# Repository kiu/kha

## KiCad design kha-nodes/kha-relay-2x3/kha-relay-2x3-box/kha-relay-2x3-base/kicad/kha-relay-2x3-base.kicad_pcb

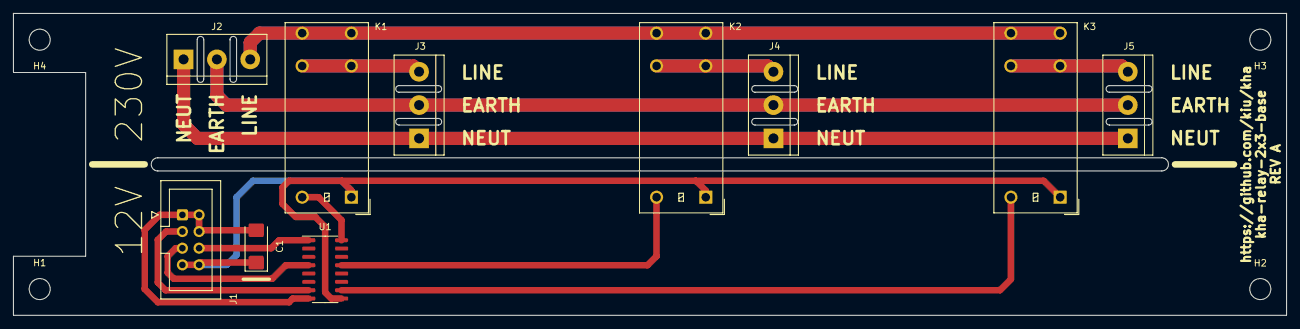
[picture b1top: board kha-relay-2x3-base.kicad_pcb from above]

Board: 2 copper layers, 194.0 x 46.0 mm, 14 parts (0 on the bottom side), 14 nets.

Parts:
C1: 220uF; CP_EIA-6032-28_Kemet-C
H1, H2, H3, H4: MountingHole; MountingHole_3.2mm_M3_DIN965
J1: Conn_02x04_Odd_Even; IDC-Header_2x04_P2.54mm_Vertical
J2, J3, J4, J5: Conn_01x03; TerminalBlock_bornier-3_P5.08mm
K1, K2, K3: G2RL-1A-E; Relay_SPST_Omron_G2RL-1A-E
U1: ULN2003; SOP-16_3.9x9.9mm_P1.27mm

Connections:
+12V: C1.1, J1.7, J1.8, K1.A1, K2.A1, K3.A1, U1.9 (COM)
Earth: J2.2, J3.2, J4.2, J5.2
GND: C1.2, J1.1, J1.2, J1.4, U1.8 (GND)
LINE: J2.3, K1.14, K2.14, K3.14
NEUT: J2.1, J3.1, J4.1, J5.1
unnamed: J1.3, U1.7 (I7)
unnamed: J1.5, U1.4 (I4)
unnamed: J1.6, U1.1 (I1)
unnamed: J3.3, K1.13
unnamed: J4.3, K2.13
unnamed: J5.3, K3.13
R01: K1.A2, U1.16 (O1)
R02: K2.A2, U1.13 (O4)
R03: K3.A2, U1.10 (O7)

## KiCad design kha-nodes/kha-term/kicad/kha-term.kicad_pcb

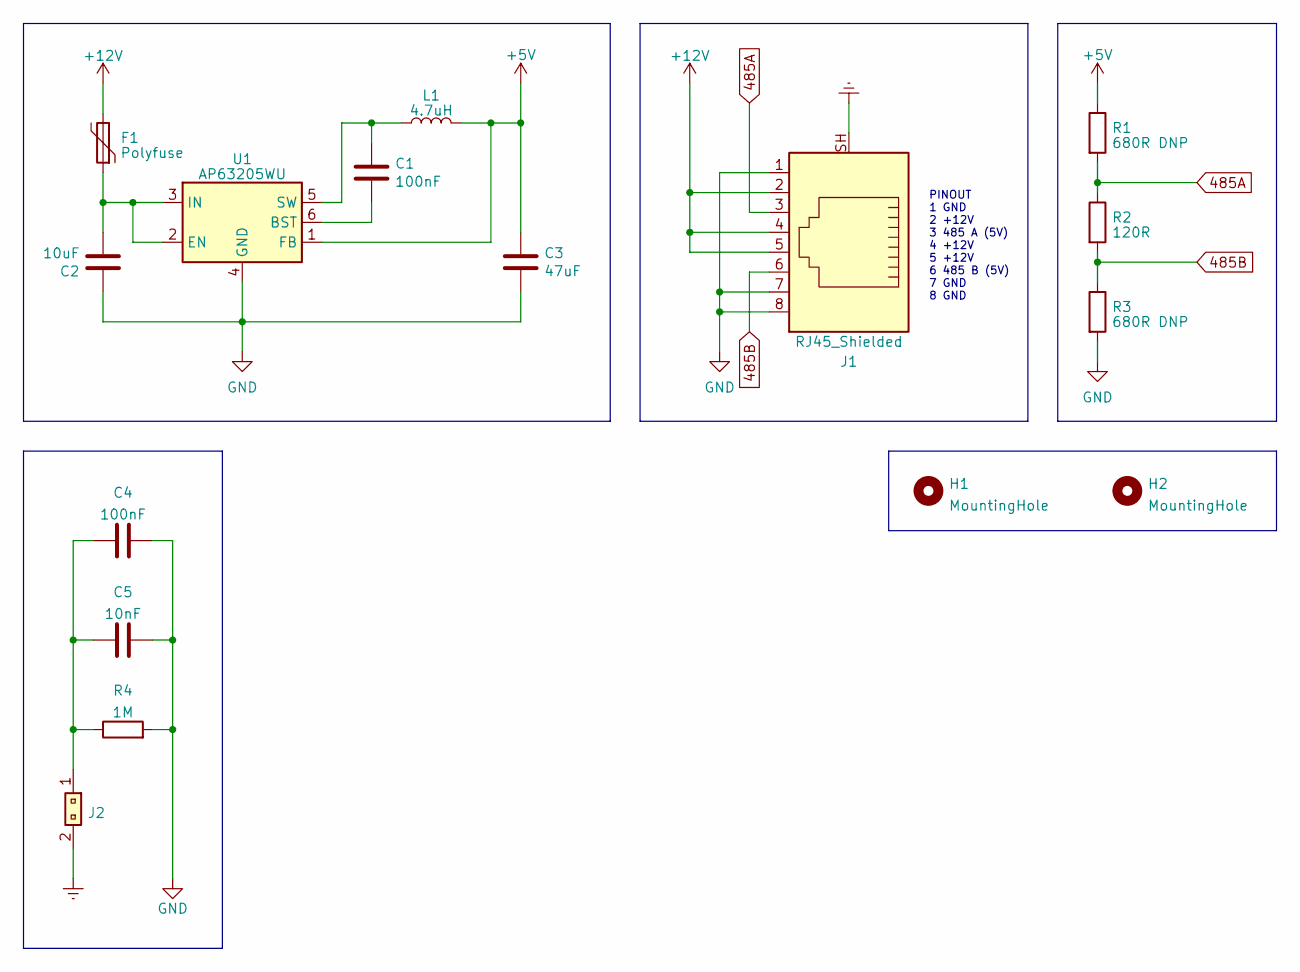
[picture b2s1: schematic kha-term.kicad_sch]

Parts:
C1, C4: 100nF; C_0805_2012Metric
C2: 10uF; C_0805_2012Metric
C3: 47uF; C_1210_3225Metric
C5: 10nF; C_0805_2012Metric
F1: Polyfuse; Fuse_0805_2012Metric
H1, H2: MountingHole; MountingHole_3.7mm
J1: RJ45_Shielded; GDLX-S-88K
J2: 1x02_Jumper; PinHeader_1x02_P2.54mm_Vertical
L1: 4.7uH; L_1210_3225Metric
R1, R3: 680R DNP; R_0805_2012Metric
R2: 120R; R_0805_2012Metric
R4: 1M; R_0805_2012Metric
U1: AP63205WU; TSOT-23-6

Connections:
485A: J1.3, R1.2, R2.1
485B: J1.6, R2.2, R3.1
+5V: C3.1, L1.2, R1.1, U1.1 (FB)
+12V: F1.2, J1.2, J1.4, J1.5
Earth: J1.SH, J2.2
GND: C2.1, C3.2, C4.2, C5.2, J1.1, J1.7, J1.8, R3.2, R4.2, U1.4 (GND)
unnamed: C4.1, C5.1, J2.1, R4.1
unnamed: C1.2, U1.6 (BST)
unnamed: C2.2, F1.1, U1.2 (EN), U1.3 (IN)
unnamed: C1.1, L1.1, U1.5 (SW)

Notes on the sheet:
PINOUT 1 GND 2 +12V 3 485 A (5V) 4 +12V 5 +12V 6 485 B (5V) 7 GND 8 GND

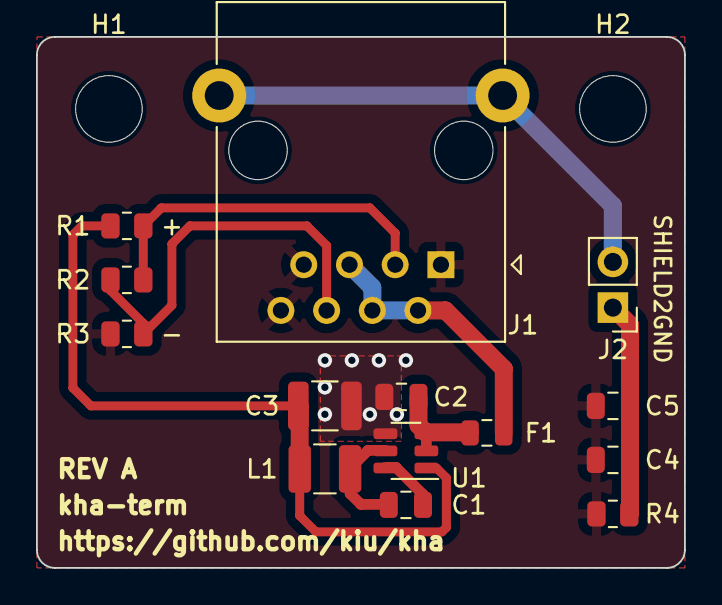
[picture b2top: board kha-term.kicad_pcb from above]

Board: 2 copper layers, 36.0 x 29.5 mm, 16 parts (0 on the bottom side), 10 nets.

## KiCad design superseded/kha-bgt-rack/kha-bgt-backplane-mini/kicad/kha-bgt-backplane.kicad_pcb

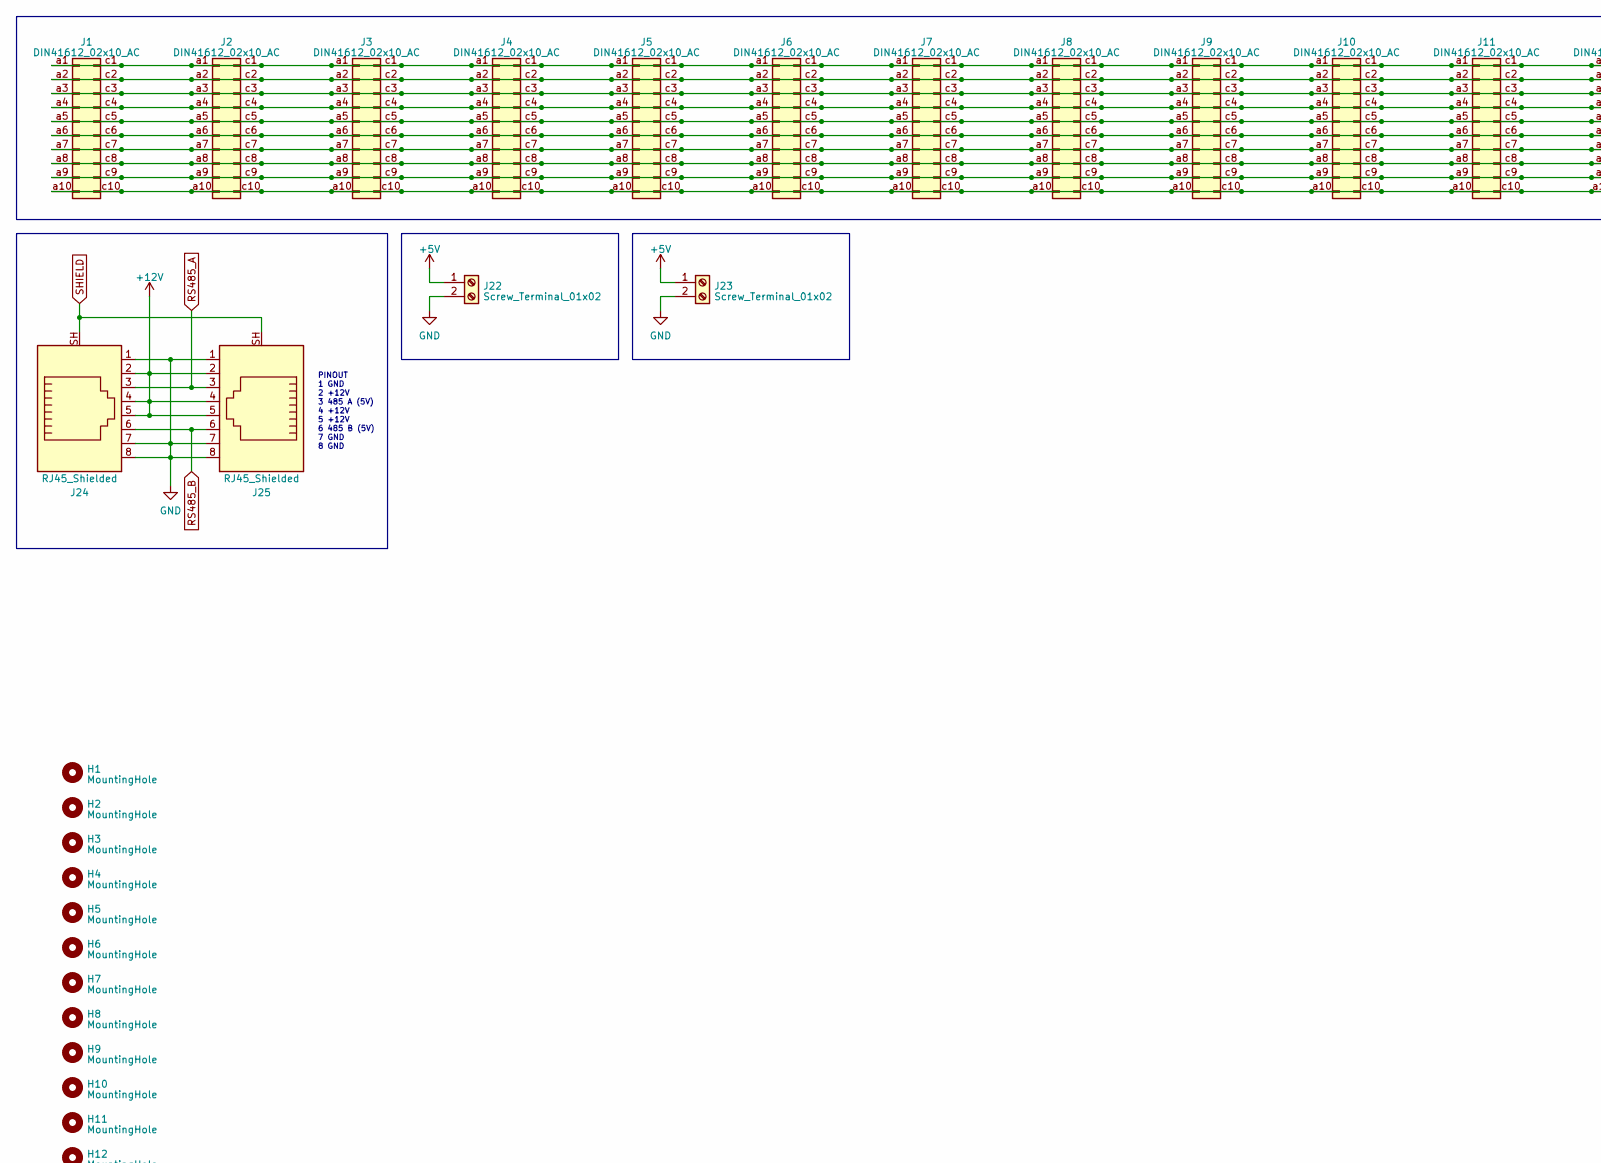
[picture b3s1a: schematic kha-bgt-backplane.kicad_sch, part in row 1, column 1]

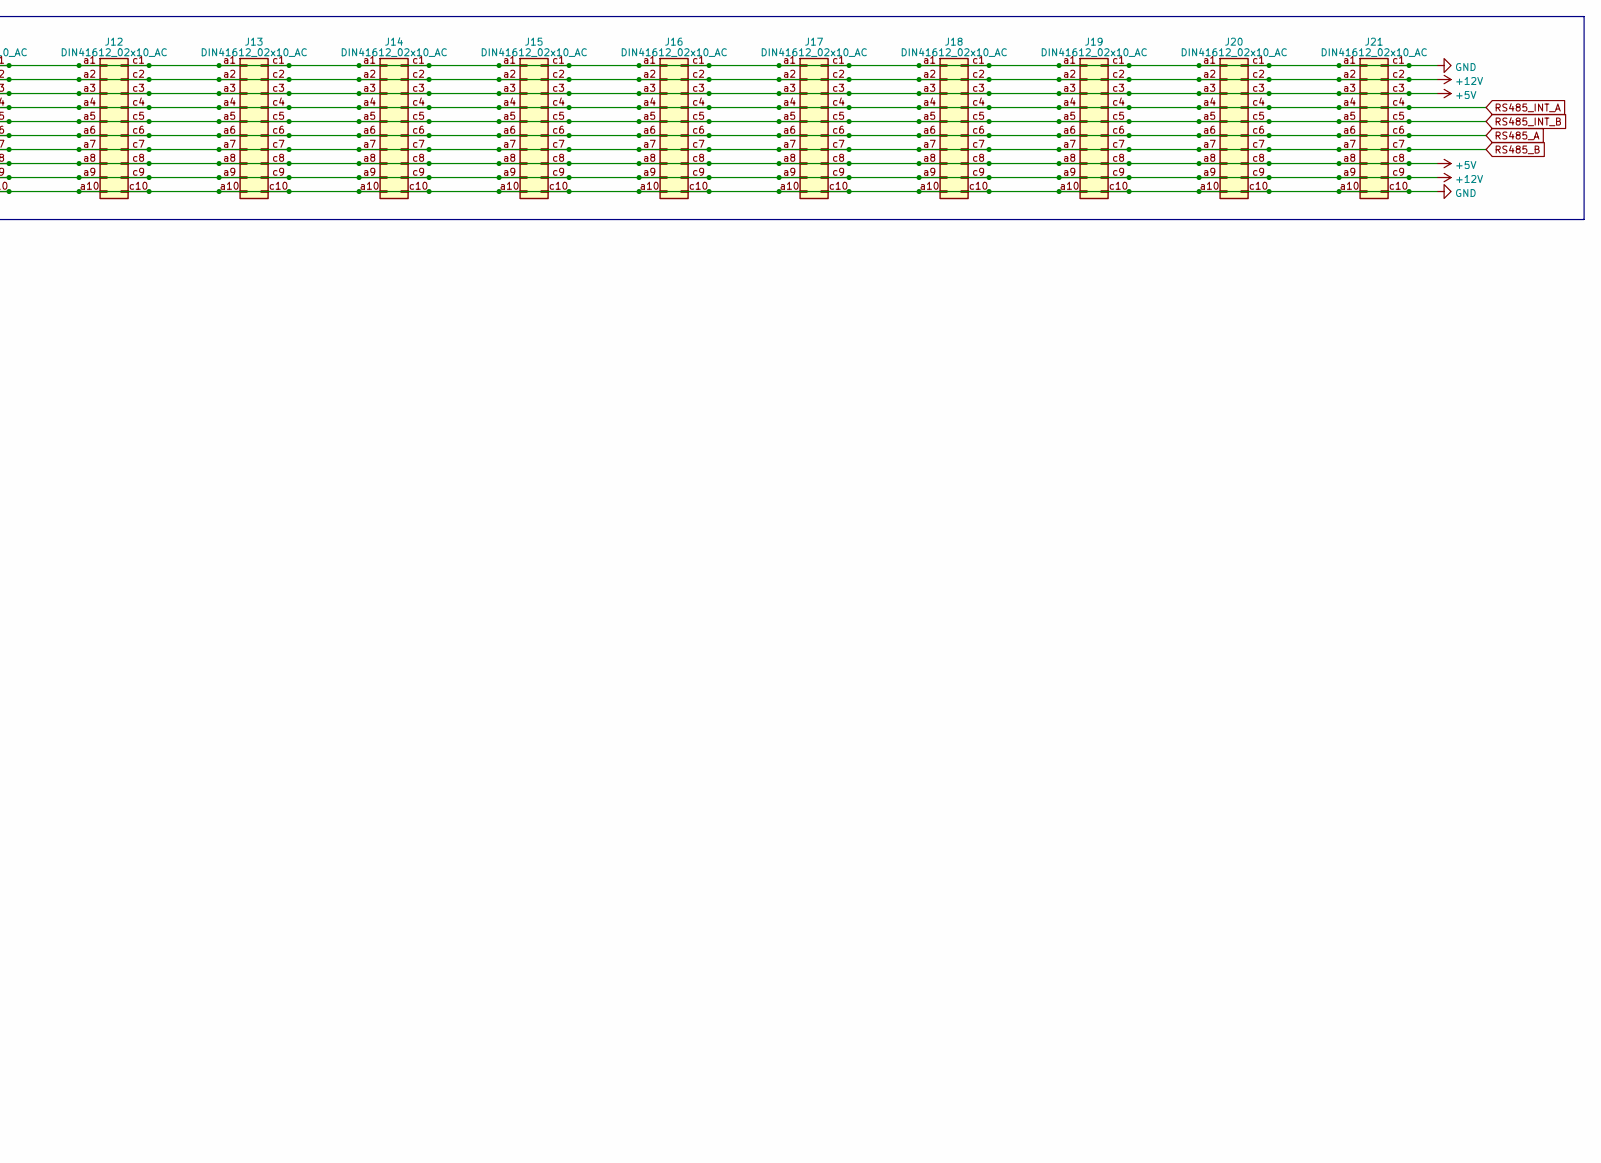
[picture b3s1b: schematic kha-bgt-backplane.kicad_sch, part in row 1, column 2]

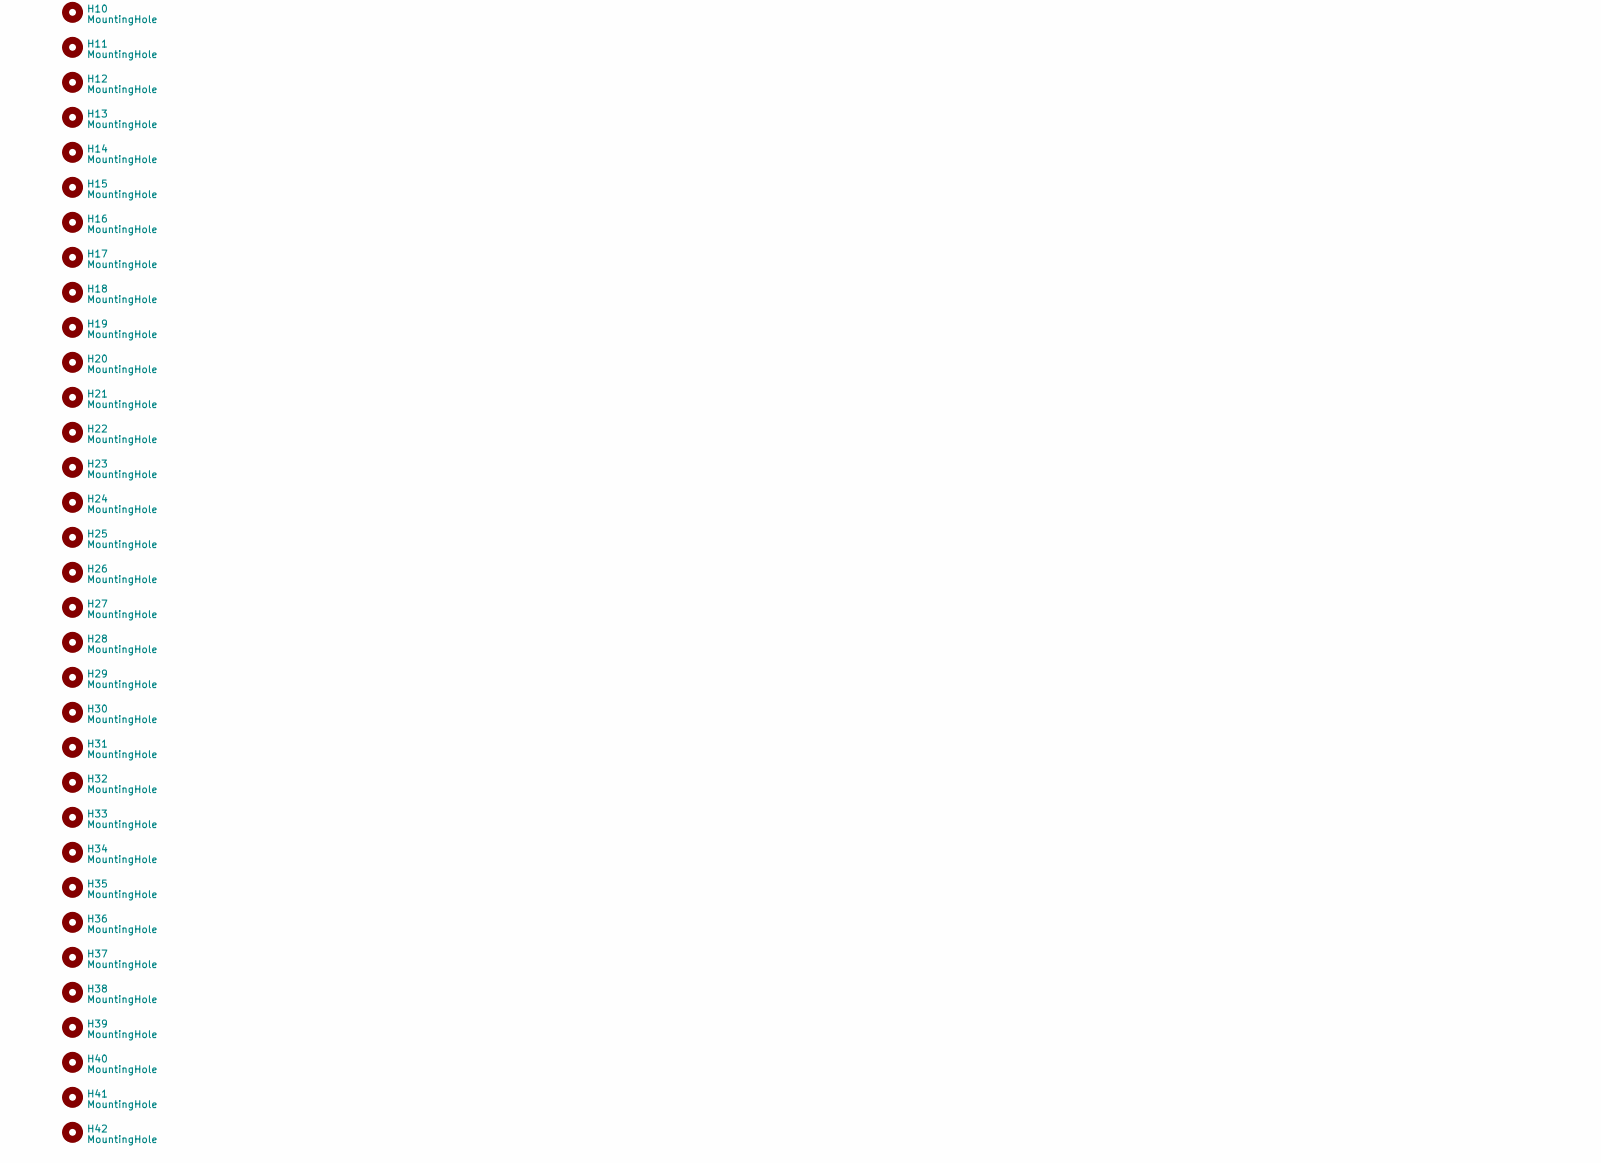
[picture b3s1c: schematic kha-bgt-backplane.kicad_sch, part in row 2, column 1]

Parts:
H1, H2, H3, H4, H5, H6, H7, H8, H9, H10, H11, H12, H13, H14, H15, H16, H17, H18, H19, H20, H21, H22, H23, H24, H25, H26, H27, H28, H29, H30, H31, H32, H33, H34, H35, H36, H37, H38, H39, H40, H41, H42: MountingHole; MountingHole_2.5mm
J1, J2, J3, J4, J5, J6, J7, J8, J9, J10, J11, J12, J13, J14, J15, J16, J17, J18, J19, J20, J21: DIN41612_02x10_AC; DIN41612_C3_2x10_Female_Vertical_THT
J22, J23: Screw_Terminal_01x02; TerminalBlock_RND_205-00232_1x02_P5.08mm_Horizontal
J24, J25: RJ45_Shielded; GDLX-S-88K

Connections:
+5V: J1.a3, J1.a8, J1.c3, J1.c8, J2.a3, J2.a8, J2.c3, J2.c8, J3.a3, J3.a8, J3.c3, J3.c8, J4.a3, J4.a8, J4.c3, J4.c8, J5.a3, J5.a8, J5.c3, J5.c8, J6.a3, J6.a8, J6.c3, J6.c8, J7.a3, J7.a8, J7.c3, J7.c8, J8.a3, J8.a8, J8.c3, J8.c8, J9.a3, J9.a8, J9.c3, J9.c8, J10.a3, J10.a8, J10.c3, J10.c8, J11.a3, J11.a8, J11.c3, J11.c8, J12.a3, J12.a8, J12.c3, J12.c8, J13.a3, J13.a8, J13.c3, J13.c8, J14.a3, J14.a8, J14.c3, J14.c8, J15.a3, J15.a8, J15.c3, J15.c8, J16.a3, J16.a8, J16.c3, J16.c8, J17.a3, J17.a8, J17.c3, J17.c8, J18.a3, J18.a8, J18.c3, J18.c8, J19.a3, J19.a8, J19.c3, J19.c8, J20.a3, J20.a8, J20.c3, J20.c8, J21.a3, J21.a8, J21.c3, J21.c8, J22.1, J23.1
+12V: J1.a2, J1.a9, J1.c2, J1.c9, J2.a2, J2.a9, J2.c2, J2.c9, J3.a2, J3.a9, J3.c2, J3.c9, J4.a2, J4.a9, J4.c2, J4.c9, J5.a2, J5.a9, J5.c2, J5.c9, J6.a2, J6.a9, J6.c2, J6.c9, J7.a2, J7.a9, J7.c2, J7.c9, J8.a2, J8.a9, J8.c2, J8.c9, J9.a2, J9.a9, J9.c2, J9.c9, J10.a2, J10.a9, J10.c2, J10.c9, J11.a2, J11.a9, J11.c2, J11.c9, J12.a2, J12.a9, J12.c2, J12.c9, J13.a2, J13.a9, J13.c2, J13.c9, J14.a2, J14.a9, J14.c2, J14.c9, J15.a2, J15.a9, J15.c2, J15.c9, J16.a2, J16.a9, J16.c2, J16.c9, J17.a2, J17.a9, J17.c2, J17.c9, J18.a2, J18.a9, J18.c2, J18.c9, J19.a2, J19.a9, J19.c2, J19.c9, J20.a2, J20.a9, J20.c2, J20.c9, J21.a2, J21.a9, J21.c2, J21.c9, J24.2, J24.4, J24.5, J25.2, J25.4, J25.5
GND: J1.a1, J1.a10, J1.c1, J1.c10, J2.a1, J2.a10, J2.c1, J2.c10, J3.a1, J3.a10, J3.c1, J3.c10, J4.a1, J4.a10, J4.c1, J4.c10, J5.a1, J5.a10, J5.c1, J5.c10, J6.a1, J6.a10, J6.c1, J6.c10, J7.a1, J7.a10, J7.c1, J7.c10, J8.a1, J8.a10, J8.c1, J8.c10, J9.a1, J9.a10, J9.c1, J9.c10, J10.a1, J10.a10, J10.c1, J10.c10, J11.a1, J11.a10, J11.c1, J11.c10, J12.a1, J12.a10, J12.c1, J12.c10, J13.a1, J13.a10, J13.c1, J13.c10, J14.a1, J14.a10, J14.c1, J14.c10, J15.a1, J15.a10, J15.c1, J15.c10, J16.a1, J16.a10, J16.c1, J16.c10, J17.a1, J17.a10, J17.c1, J17.c10, J18.a1, J18.a10, J18.c1, J18.c10, J19.a1, J19.a10, J19.c1, J19.c10, J20.a1, J20.a10, J20.c1, J20.c10, J21.a1, J21.a10, J21.c1, J21.c10, J22.2, J23.2, J24.1, J24.7, J24.8, J25.1, J25.7, J25.8
RS485_A: J1.a6, J1.c6, J2.a6, J2.c6, J3.a6, J3.c6, J4.a6, J4.c6, J5.a6, J5.c6, J6.a6, J6.c6, J7.a6, J7.c6, J8.a6, J8.c6, J9.a6, J9.c6, J10.a6, J10.c6, J11.a6, J11.c6, J12.a6, J12.c6, J13.a6, J13.c6, J14.a6, J14.c6, J15.a6, J15.c6, J16.a6, J16.c6, J17.a6, J17.c6, J18.a6, J18.c6, J19.a6, J19.c6, J20.a6, J20.c6, J21.a6, J21.c6, J24.3, J25.3
RS485_B: J1.a7, J1.c7, J2.a7, J2.c7, J3.a7, J3.c7, J4.a7, J4.c7, J5.a7, J5.c7, J6.a7, J6.c7, J7.a7, J7.c7, J8.a7, J8.c7, J9.a7, J9.c7, J10.a7, J10.c7, J11.a7, J11.c7, J12.a7, J12.c7, J13.a7, J13.c7, J14.a7, J14.c7, J15.a7, J15.c7, J16.a7, J16.c7, J17.a7, J17.c7, J18.a7, J18.c7, J19.a7, J19.c7, J20.a7, J20.c7, J21.a7, J21.c7, J24.6, J25.6
RS485_INT_A: J1.a4, J1.c4, J2.a4, J2.c4, J3.a4, J3.c4, J4.a4, J4.c4, J5.a4, J5.c4, J6.a4, J6.c4, J7.a4, J7.c4, J8.a4, J8.c4, J9.a4, J9.c4, J10.a4, J10.c4, J11.a4, J11.c4, J12.a4, J12.c4, J13.a4, J13.c4, J14.a4, J14.c4, J15.a4, J15.c4, J16.a4, J16.c4, J17.a4, J17.c4, J18.a4, J18.c4, J19.a4, J19.c4, J20.a4, J20.c4, J21.a4, J21.c4
RS485_INT_B: J1.a5, J1.c5, J2.a5, J2.c5, J3.a5, J3.c5, J4.a5, J4.c5, J5.a5, J5.c5, J6.a5, J6.c5, J7.a5, J7.c5, J8.a5, J8.c5, J9.a5, J9.c5, J10.a5, J10.c5, J11.a5, J11.c5, J12.a5, J12.c5, J13.a5, J13.c5, J14.a5, J14.c5, J15.a5, J15.c5, J16.a5, J16.c5, J17.a5, J17.c5, J18.a5, J18.c5, J19.a5, J19.c5, J20.a5, J20.c5, J21.a5, J21.c5
SHIELD: J24.SH, J25.SH

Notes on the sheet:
PINOUT 1 GND 2 +12V 3 485 A (5V) 4 +12V 5 +12V 6 485 B (5V) 7 GND 8 GND

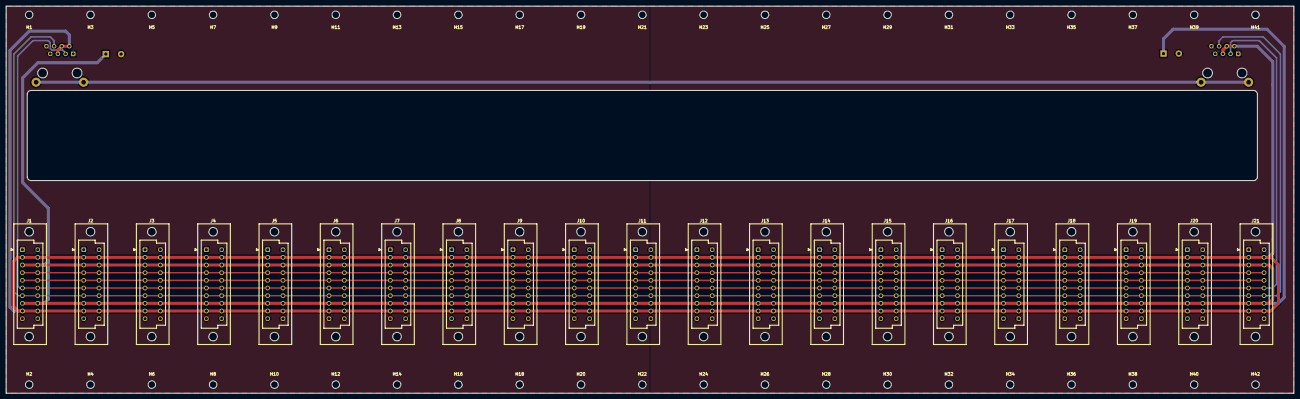
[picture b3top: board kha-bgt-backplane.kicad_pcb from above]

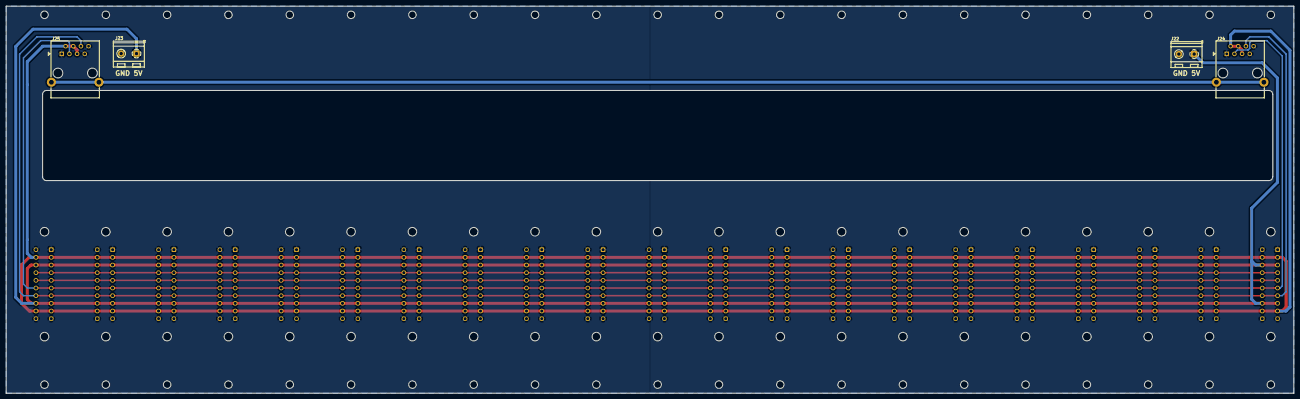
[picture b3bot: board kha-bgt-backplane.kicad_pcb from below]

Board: 2 copper layers, 426.7 x 128.3 mm, 67 parts (4 on the bottom side), 8 nets.

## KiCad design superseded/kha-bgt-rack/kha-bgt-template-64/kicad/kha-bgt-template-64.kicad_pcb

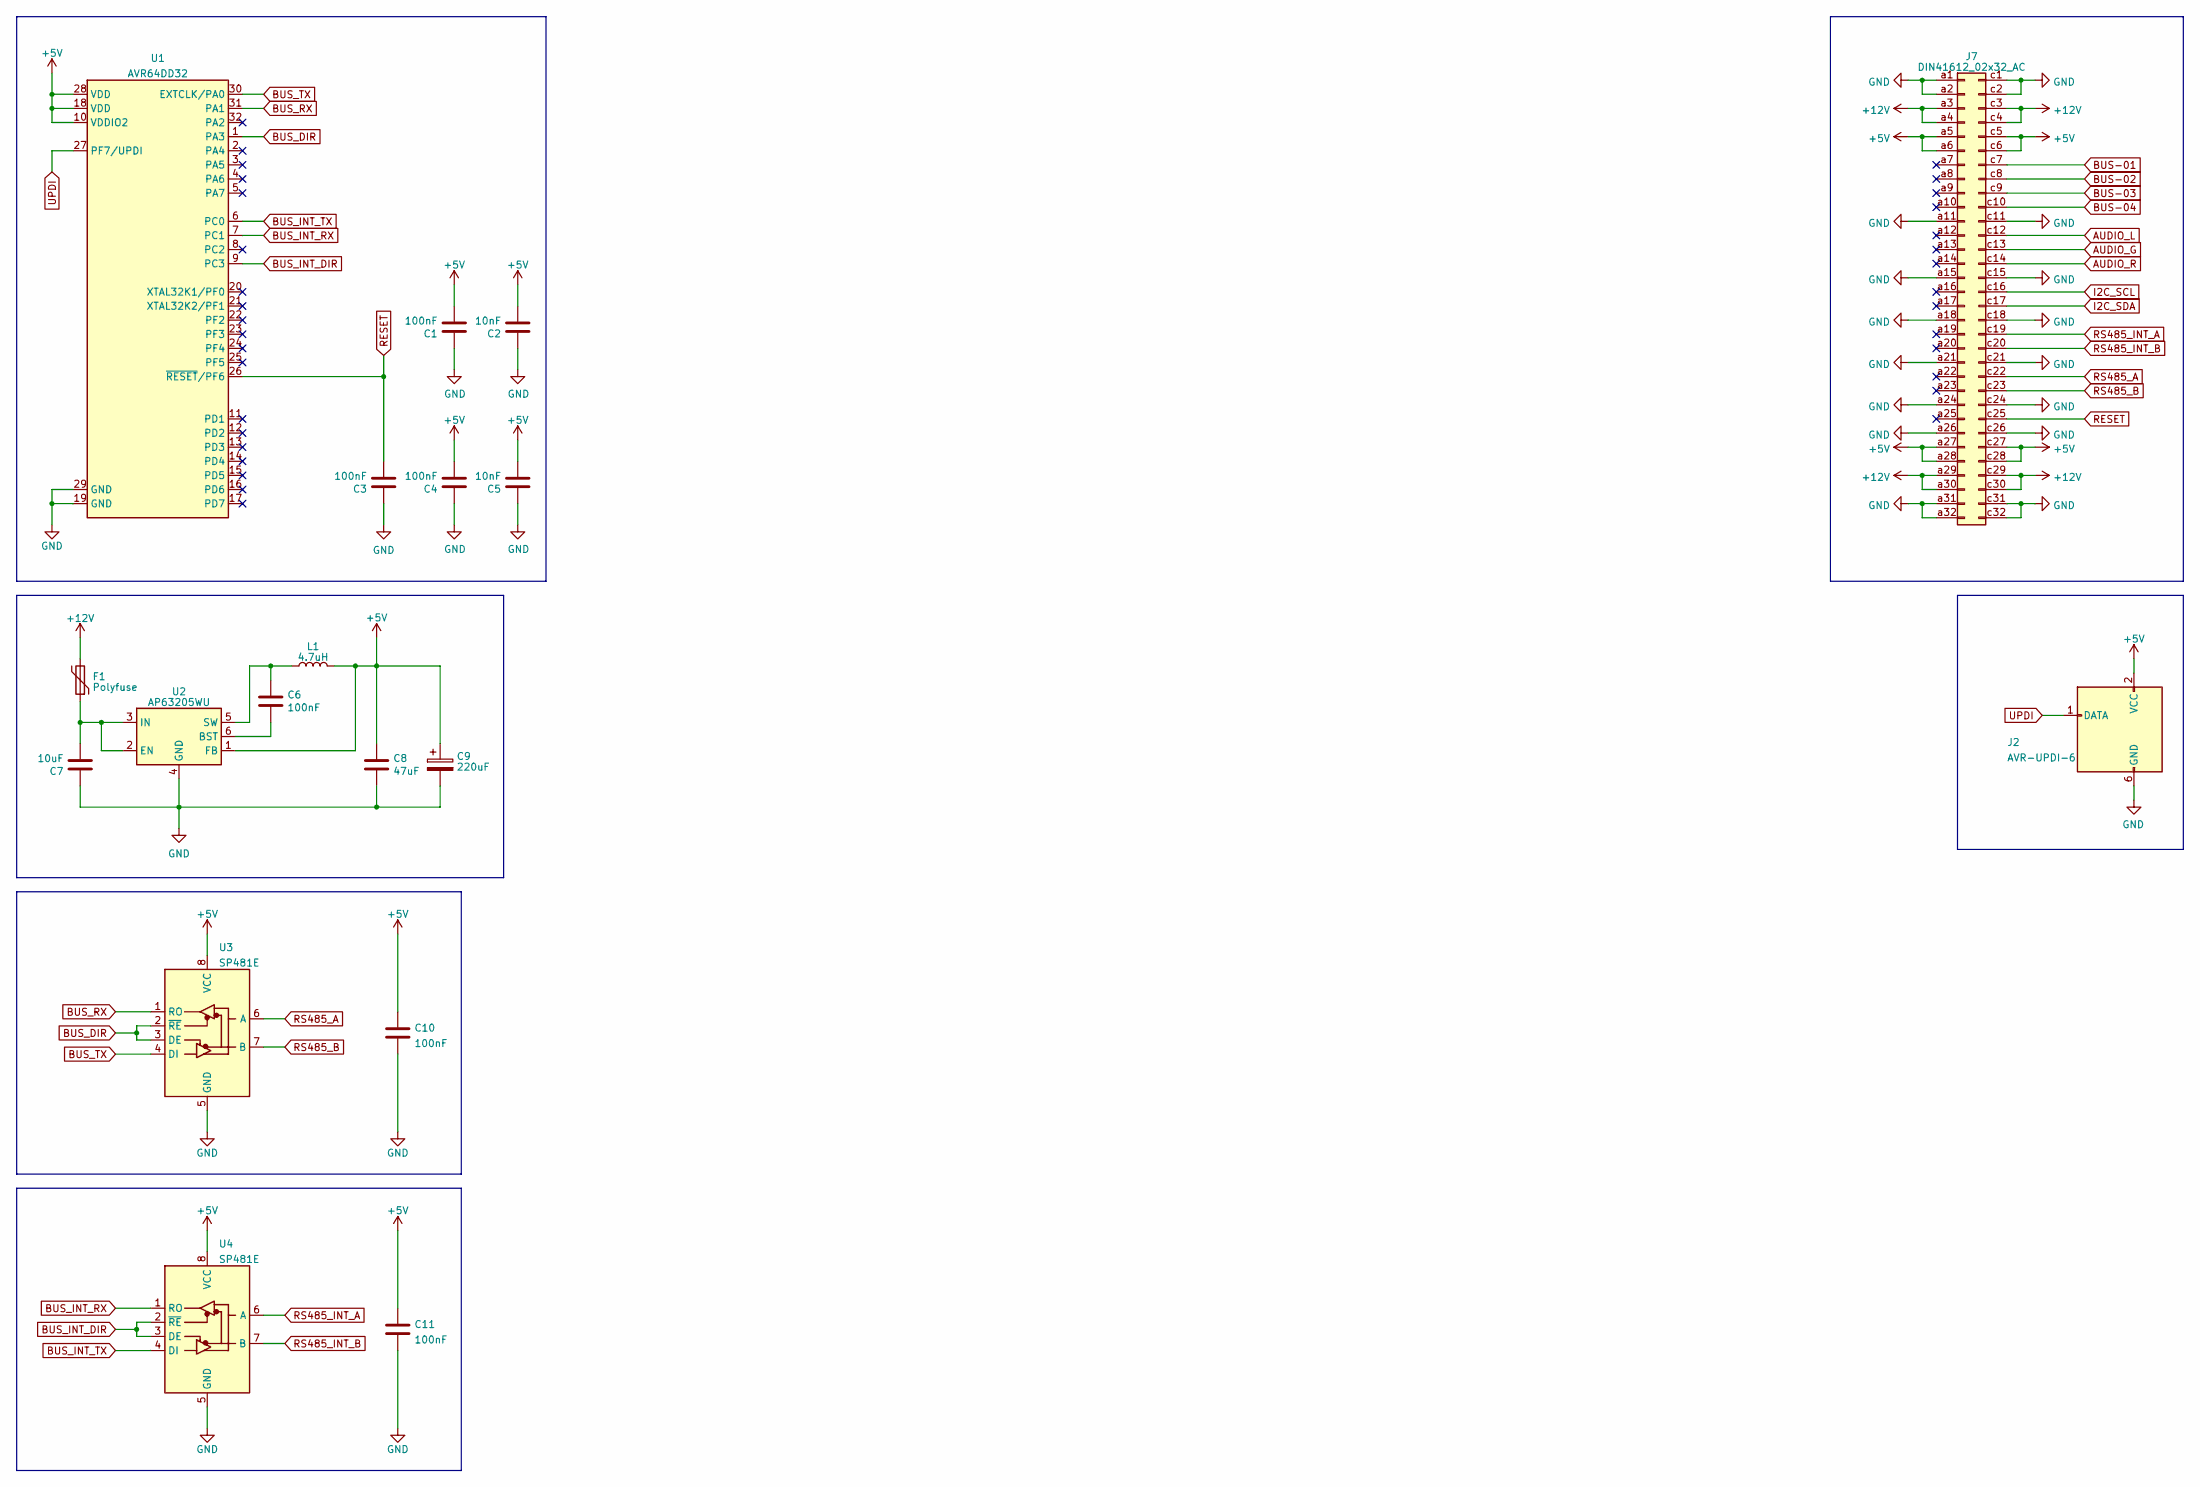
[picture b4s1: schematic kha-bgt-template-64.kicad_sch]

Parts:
C1, C3, C4, C6, C10, C11: 100nF; C_0805_2012Metric
C2, C5: 10nF; C_0805_2012Metric
C7: 10uF; C_0805_2012Metric
C8: 47uF; C_1210_3225Metric
C9: 220uF; CP_EIA-6032-28_Kemet-C
F1: Polyfuse; Fuse_0805_2012Metric
J2: AVR-UPDI-6; eAVR6-UPDI-B
J7: DIN41612_02x32_AC; DIN41612_C_2x32_Male_Horizontal_THT
L1: 4.7uH; L_1210_3225Metric
U1: AVR64DD32; TQFP-32_7x7mm_P0.8mm
U2: AP63205WU; TSOT-23-6
U3, U4: SP481E; SOIC-8_3.9x4.9mm_P1.27mm

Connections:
+5V: C1.2, C2.2, C4.2, C5.2, C8.1, C9.1, C10.1, C11.1, J2.2 (VCC), J7.a5, J7.a6, J7.a27, J7.a28, J7.c5, J7.c6, J7.c27, J7.c28, L1.2, U1.10 (VDDIO2), U1.18 (VDD), U1.28 (VDD), U2.1 (FB), U3.8 (VCC), U4.8 (VCC)
+12V: F1.2, J7.a3, J7.a4, J7.a29, J7.a30, J7.c3, J7.c4, J7.c29, J7.c30
AUDIO_G: J7.c13
AUDIO_L: J7.c12
AUDIO_R: J7.c14
BUS-01: J7.c7
BUS-02: J7.c8
BUS-03: J7.c9
BUS-04: J7.c10
BUS_DIR: U1.1 (PA3), U3.2 (~RE), U3.3 (DE)
BUS_INT_DIR: U1.9 (PC3), U4.2 (~RE), U4.3 (DE)
BUS_INT_RX: U1.7 (PC1), U4.1 (RO)
BUS_INT_TX: U1.6 (PC0), U4.4 (DI)
BUS_RX: U1.31 (PA1), U3.1 (RO)
BUS_TX: U1.30 (EXTCLK/PA0), U3.4 (DI)
GND: C1.1, C2.1, C3.1, C4.1, C5.1, C7.1, C8.2, C9.2, C10.2, C11.2, J2.6 (GND), J7.a1, J7.a2, J7.a11, J7.a15, J7.a18, J7.a21, J7.a24, J7.a26, J7.a31, J7.a32, J7.c1, J7.c2, J7.c11, J7.c15, J7.c18, J7.c21, J7.c24, J7.c26, J7.c31, J7.c32, U1.19 (GND), U1.29 (GND), U2.4 (GND), U3.5 (GND), U4.5 (GND)
I2C_SCL: J7.c16
I2C_SDA: J7.c17
unnamed: C6.2, U2.6 (BST)
unnamed: C7.2, F1.1, U2.2 (EN), U2.3 (IN)
unnamed: C6.1, L1.1, U2.5 (SW)
RESET: C3.2, J7.c25, U1.26 (~RESET/PF6)
RS485_A: J7.c22, U3.6 (A)
RS485_B: J7.c23, U3.7 (B)
RS485_INT_A: J7.c19, U4.6 (A)
RS485_INT_B: J7.c20, U4.7 (B)
UPDI: J2.1 (DATA), U1.27 (PF7/UPDI)

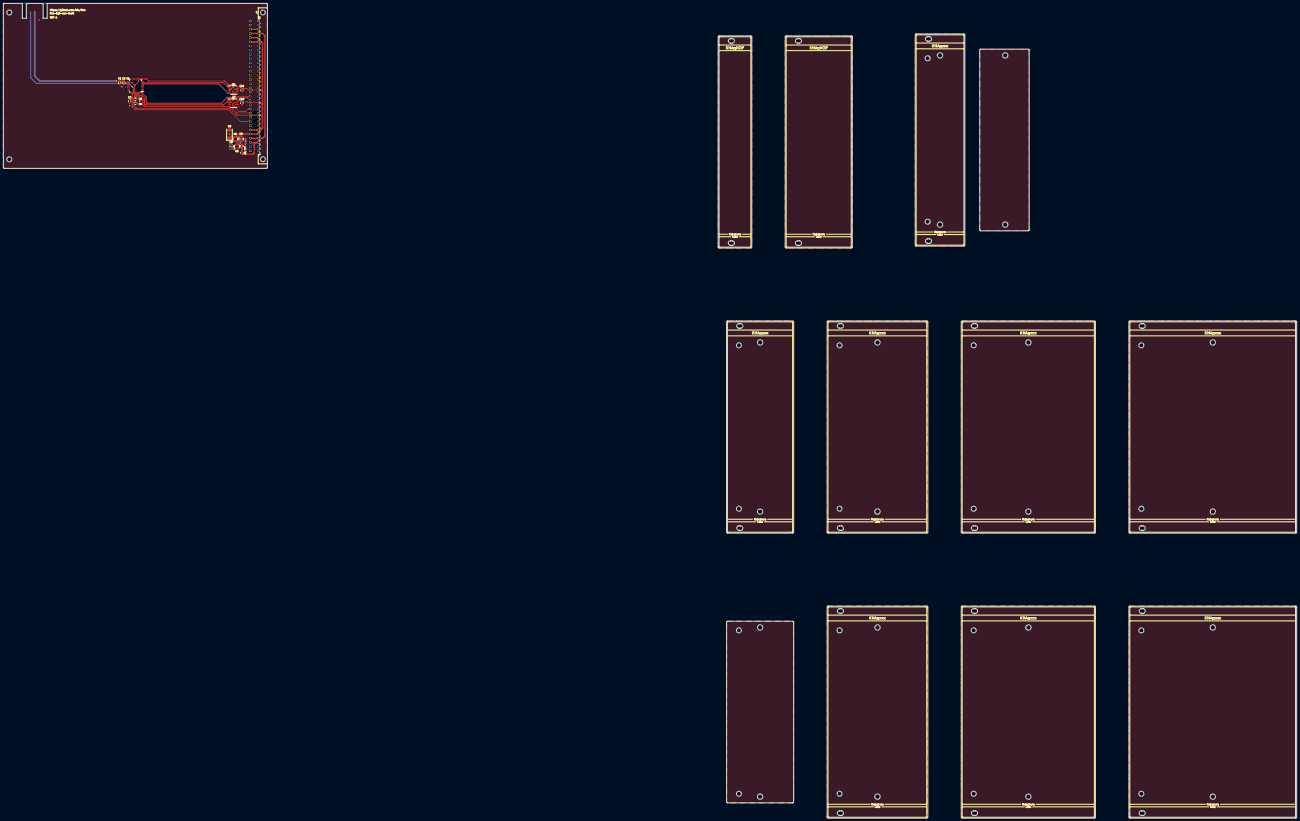
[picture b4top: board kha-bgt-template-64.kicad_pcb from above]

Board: 2 copper layers, 160.0 x 100.0 mm, 19 parts (0 on the bottom side), 18 nets.

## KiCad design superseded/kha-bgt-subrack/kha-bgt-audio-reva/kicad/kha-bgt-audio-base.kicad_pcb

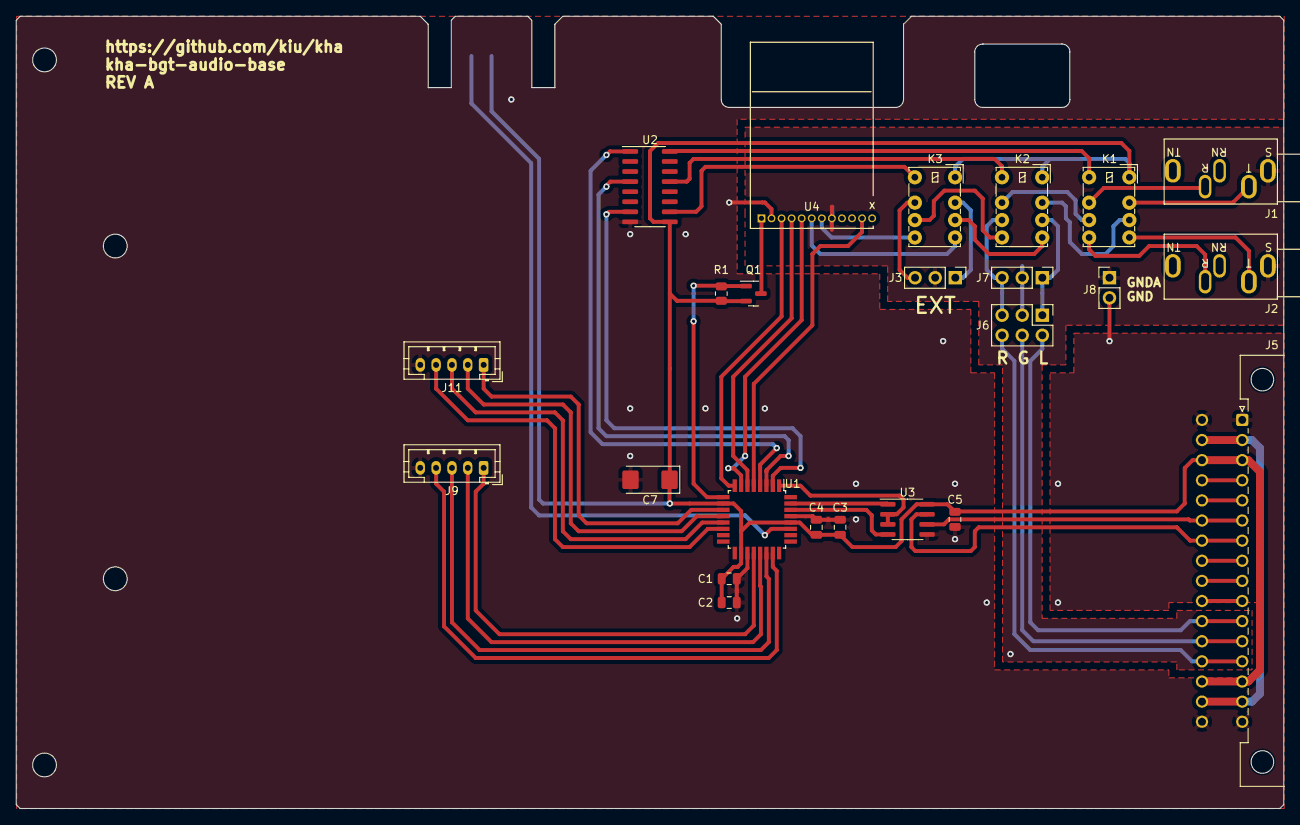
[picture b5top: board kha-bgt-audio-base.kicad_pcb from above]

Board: 2 copper layers, 160.0 x 100.0 mm, 25 parts (1 on the bottom side), 52 nets.

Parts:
C1, C4: 10nF; C_0805_2012Metric
C2, C3, C5: 100nF; C_0805_2012Metric
C7: 220uF; CP_EIA-6032-28_Kemet-C
J1, J2: AudioJack3; PJ-325C5
J3, J7: Conn_01x03; PinHeader_1x03_P2.54mm_Vertical
J4: AVR-UPDI-6; eAVR6-UPDI-F
J5: DIN41612_02x16_AC; DIN41612_C2_2x16_Male_Horizontal_THT
J6: Conn_02x03_Odd_Even; PinHeader_2x03_P2.54mm_Vertical
J8: 1x02_Jumper; PinHeader_1x02_P2.54mm_Vertical
J9, J11: Conn_01x05; JST_PH_B5B-PH-K_1x05_P2.00mm_Vertical
K1, K2, K3: HFD4/5; Relay_DPDT_HDF4-5
Q1: DMG2301L; SOT-23
R1: 10k; R_0805_2012Metric
U1: AVR64DD32; TQFP-32_7x7mm_P0.8mm
U2: ULN2003; SOP-16_3.9x9.9mm_P1.27mm
U3: SP481E; SOIC-8_3.9x4.9mm_P1.27mm
U4: KCX_BT_EMITTER_1.7; KCX_BT_EMITTER_V1.7 12P

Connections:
+5V: C1.1, C2.1, C3.1, C4.1, C5.1, C7.1, J4.2 (VCC), J5.a3, J5.a14, J5.c3, J5.c14, K1.1, K2.1, K3.1, Q1.2 (S), R1.1, U1.10 (VDDIO2), U1.18 (VDD), U1.28 (VDD), U2.9 (COM), U3.8 (VCC)
+12V: J5.a2, J5.a15, J5.c2, J5.c15
AUDIO_LEFT: J6.1, J7.1, K2.3
AUDIO_RIGHT: J6.5, J7.3, K2.6
BTN01: J11.1, U1.11 (PD1)
BTN02: J11.3, U1.13 (PD3)
BTN03: J9.1, U1.20 (XTAL32K1/PF0)
BTN04: J9.3, U1.22 (PF2)
BT_CON: U1.5 (PA7), U4.11 (CON)
BT_LNK: U1.8 (PC2), U4.3 (LINK)
BT_RX: U1.6 (PC0), U4.4 (RX)
BT_TX: U1.7 (PC1), U4.5 (TX)
BT_VCC: Q1.3 (D), U4.1 (+5V)
BUS01: J5.a8, J5.c8
BUS02: J5.a9, J5.c9
BUS03: J5.a10, J5.c10
BUS04: J5.a11, J5.c11, J6.2
BUS05: J5.a12, J5.c12, J6.4
BUS06: J5.a13, J5.c13, J6.6
BUS_DIR: U1.1 (PA3), U3.2 (~RE), U3.3 (DE)
BUS_RX: U1.31 (PA1), U3.1 (RO)
BUS_TX: U1.30 (EXTCLK/PA0), U3.4 (DI)
GND: C1.2, C2.2, C3.2, C4.2, C5.2, C7.2, J4.6 (GND), J5.a1, J5.a16, J5.c1, J5.c16, J8.2, J9.5, J11.5, U1.19 (GND), U1.29 (GND), U2.8 (GND), U3.5 (GND), U4.2 (GND)
GNDA: J1.S, J2.S, J3.2, J6.3, J7.2, J8.1, U4.8 (AGND)
LED01: J11.2, U1.12 (PD2)
LED02: J11.4, U1.14 (PD4)
LED03: J9.2, U1.21 (XTAL32K2/PF1)
LED04: J9.4, U1.23 (PF3)
unnamed: J1.R, K1.7
unnamed: J1.T, K1.2
unnamed: J2.R, K1.5
unnamed: J2.T, K1.4
unnamed: J3.1, K3.2
unnamed: J3.3, K3.7
unnamed: K1.3, K2.2
unnamed: K1.6, K2.7
unnamed: K2.4, K3.3
unnamed: K2.5, K3.6
unnamed: K3.4, U4.6 (LEFT)
unnamed: K3.5, U4.7 (RIGHT)
R01: K1.8, U2.16 (O1)
R02: K3.8, U2.10 (O7)
R03: K2.8, U2.13 (O4)
RS485_A: J5.a6, J5.c6, U3.6 (A)
RS485_B: J5.a7, J5.c7, U3.7 (B)
RS485_INT_A: J5.a4, J5.c4
RS485_INT_B: J5.a5, J5.c5
SR01: U1.4 (PA6), U2.1 (I1)
SR02: U1.2 (PA4), U2.7 (I7)
SR03: U1.3 (PA5), U2.4 (I4)
S_BT_VCC: Q1.1 (G), R1.2, U1.9 (PC3)
UPDI: J4.1 (DATA), U1.27 (PF7/UPDI)
